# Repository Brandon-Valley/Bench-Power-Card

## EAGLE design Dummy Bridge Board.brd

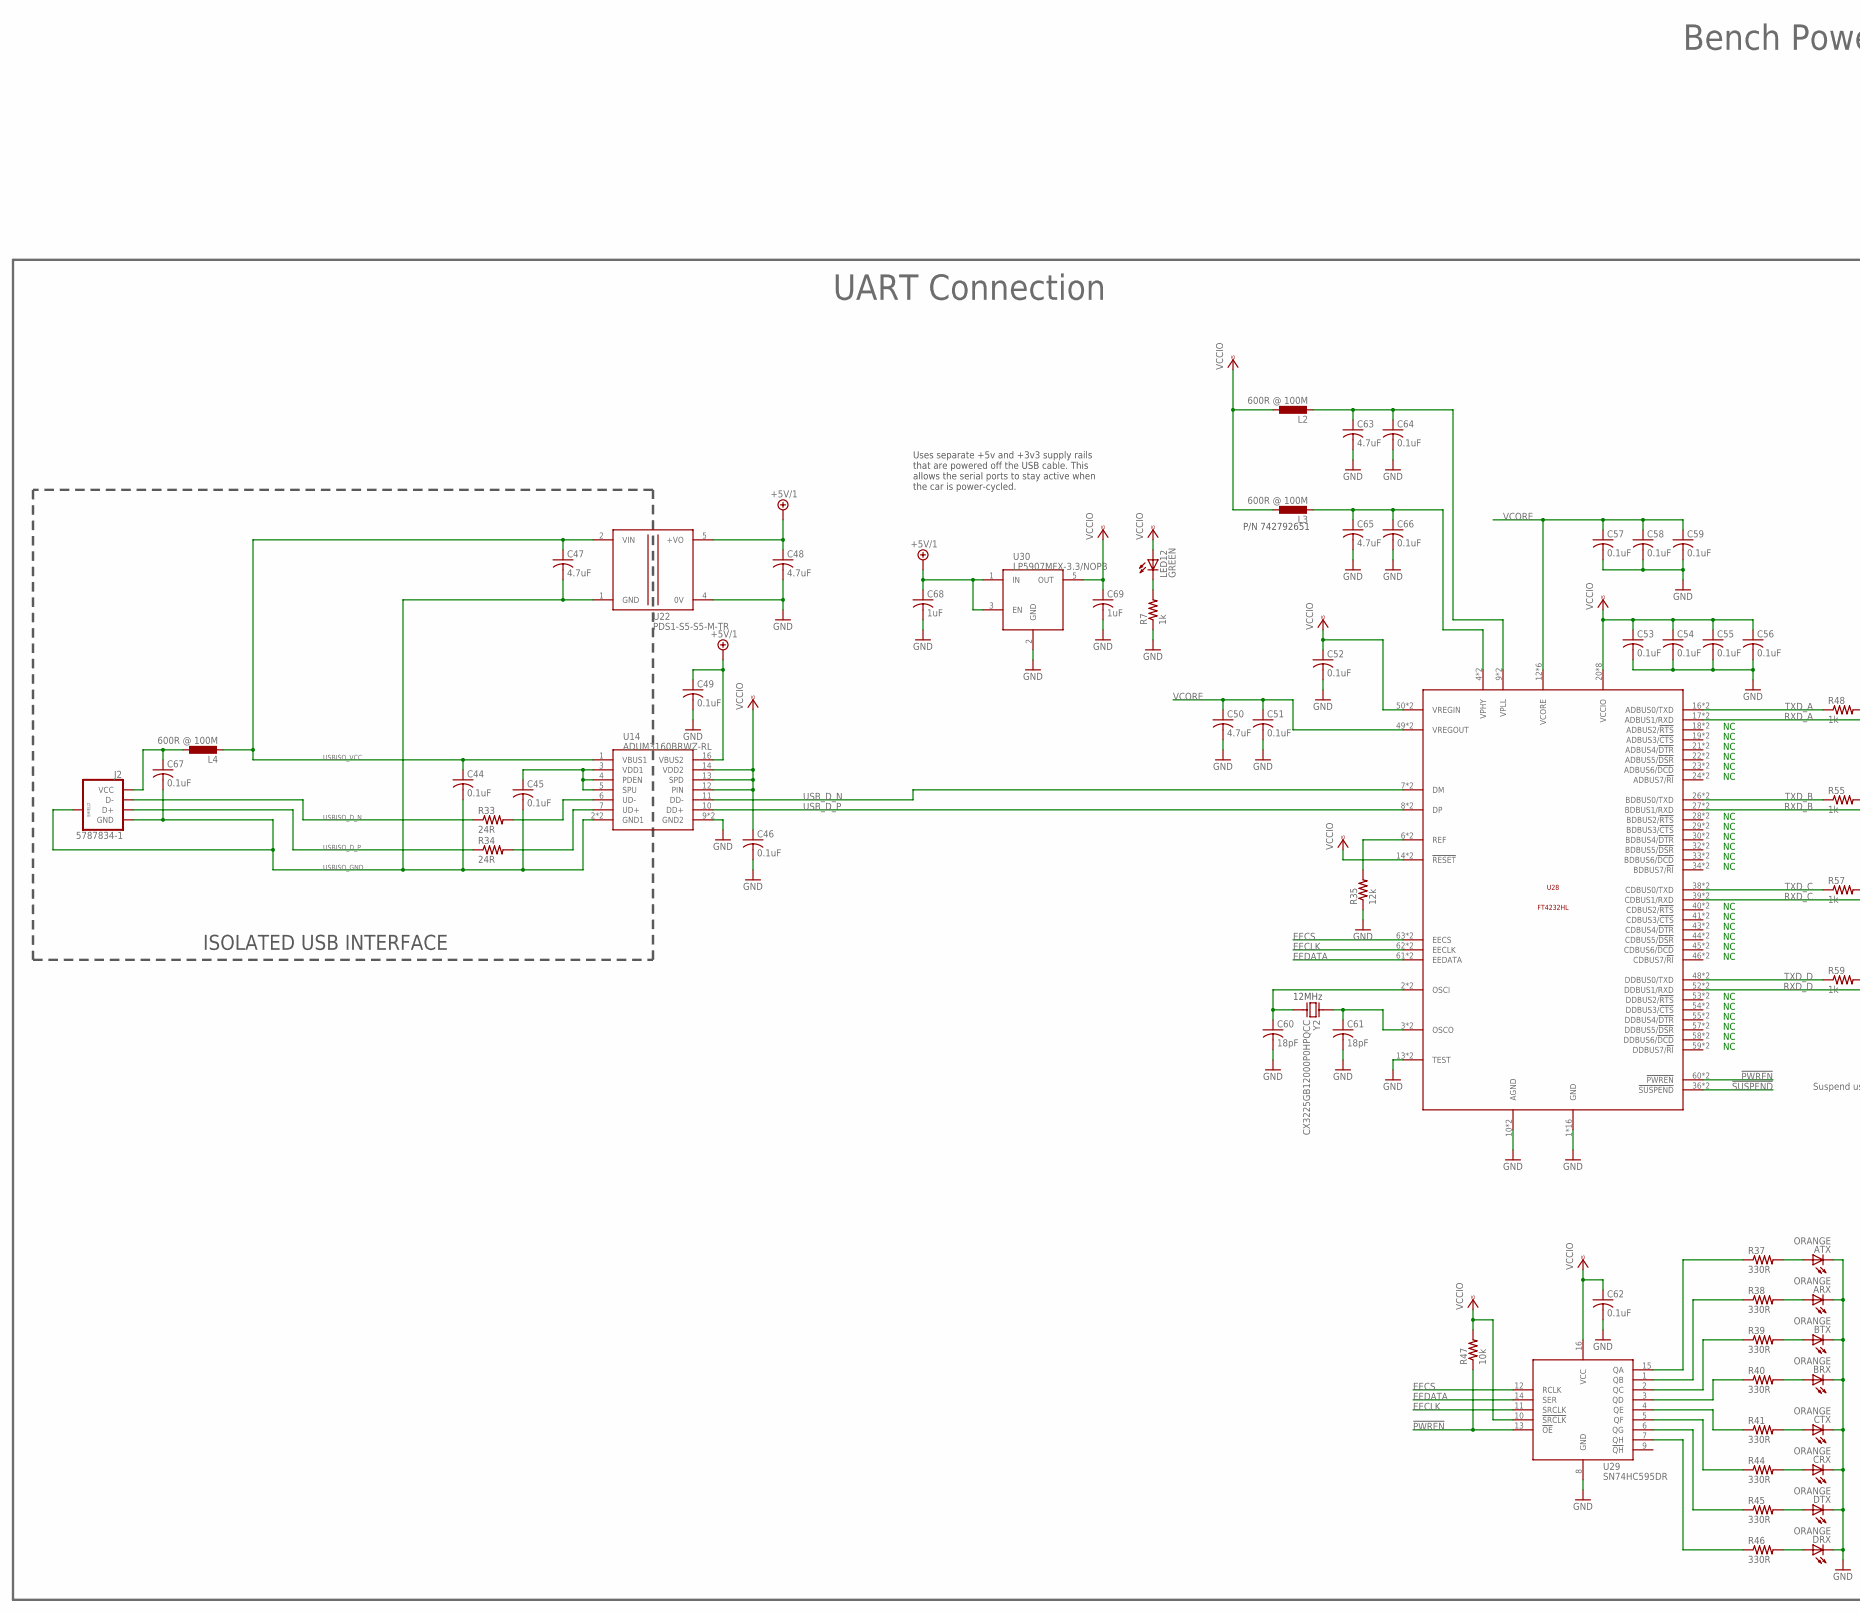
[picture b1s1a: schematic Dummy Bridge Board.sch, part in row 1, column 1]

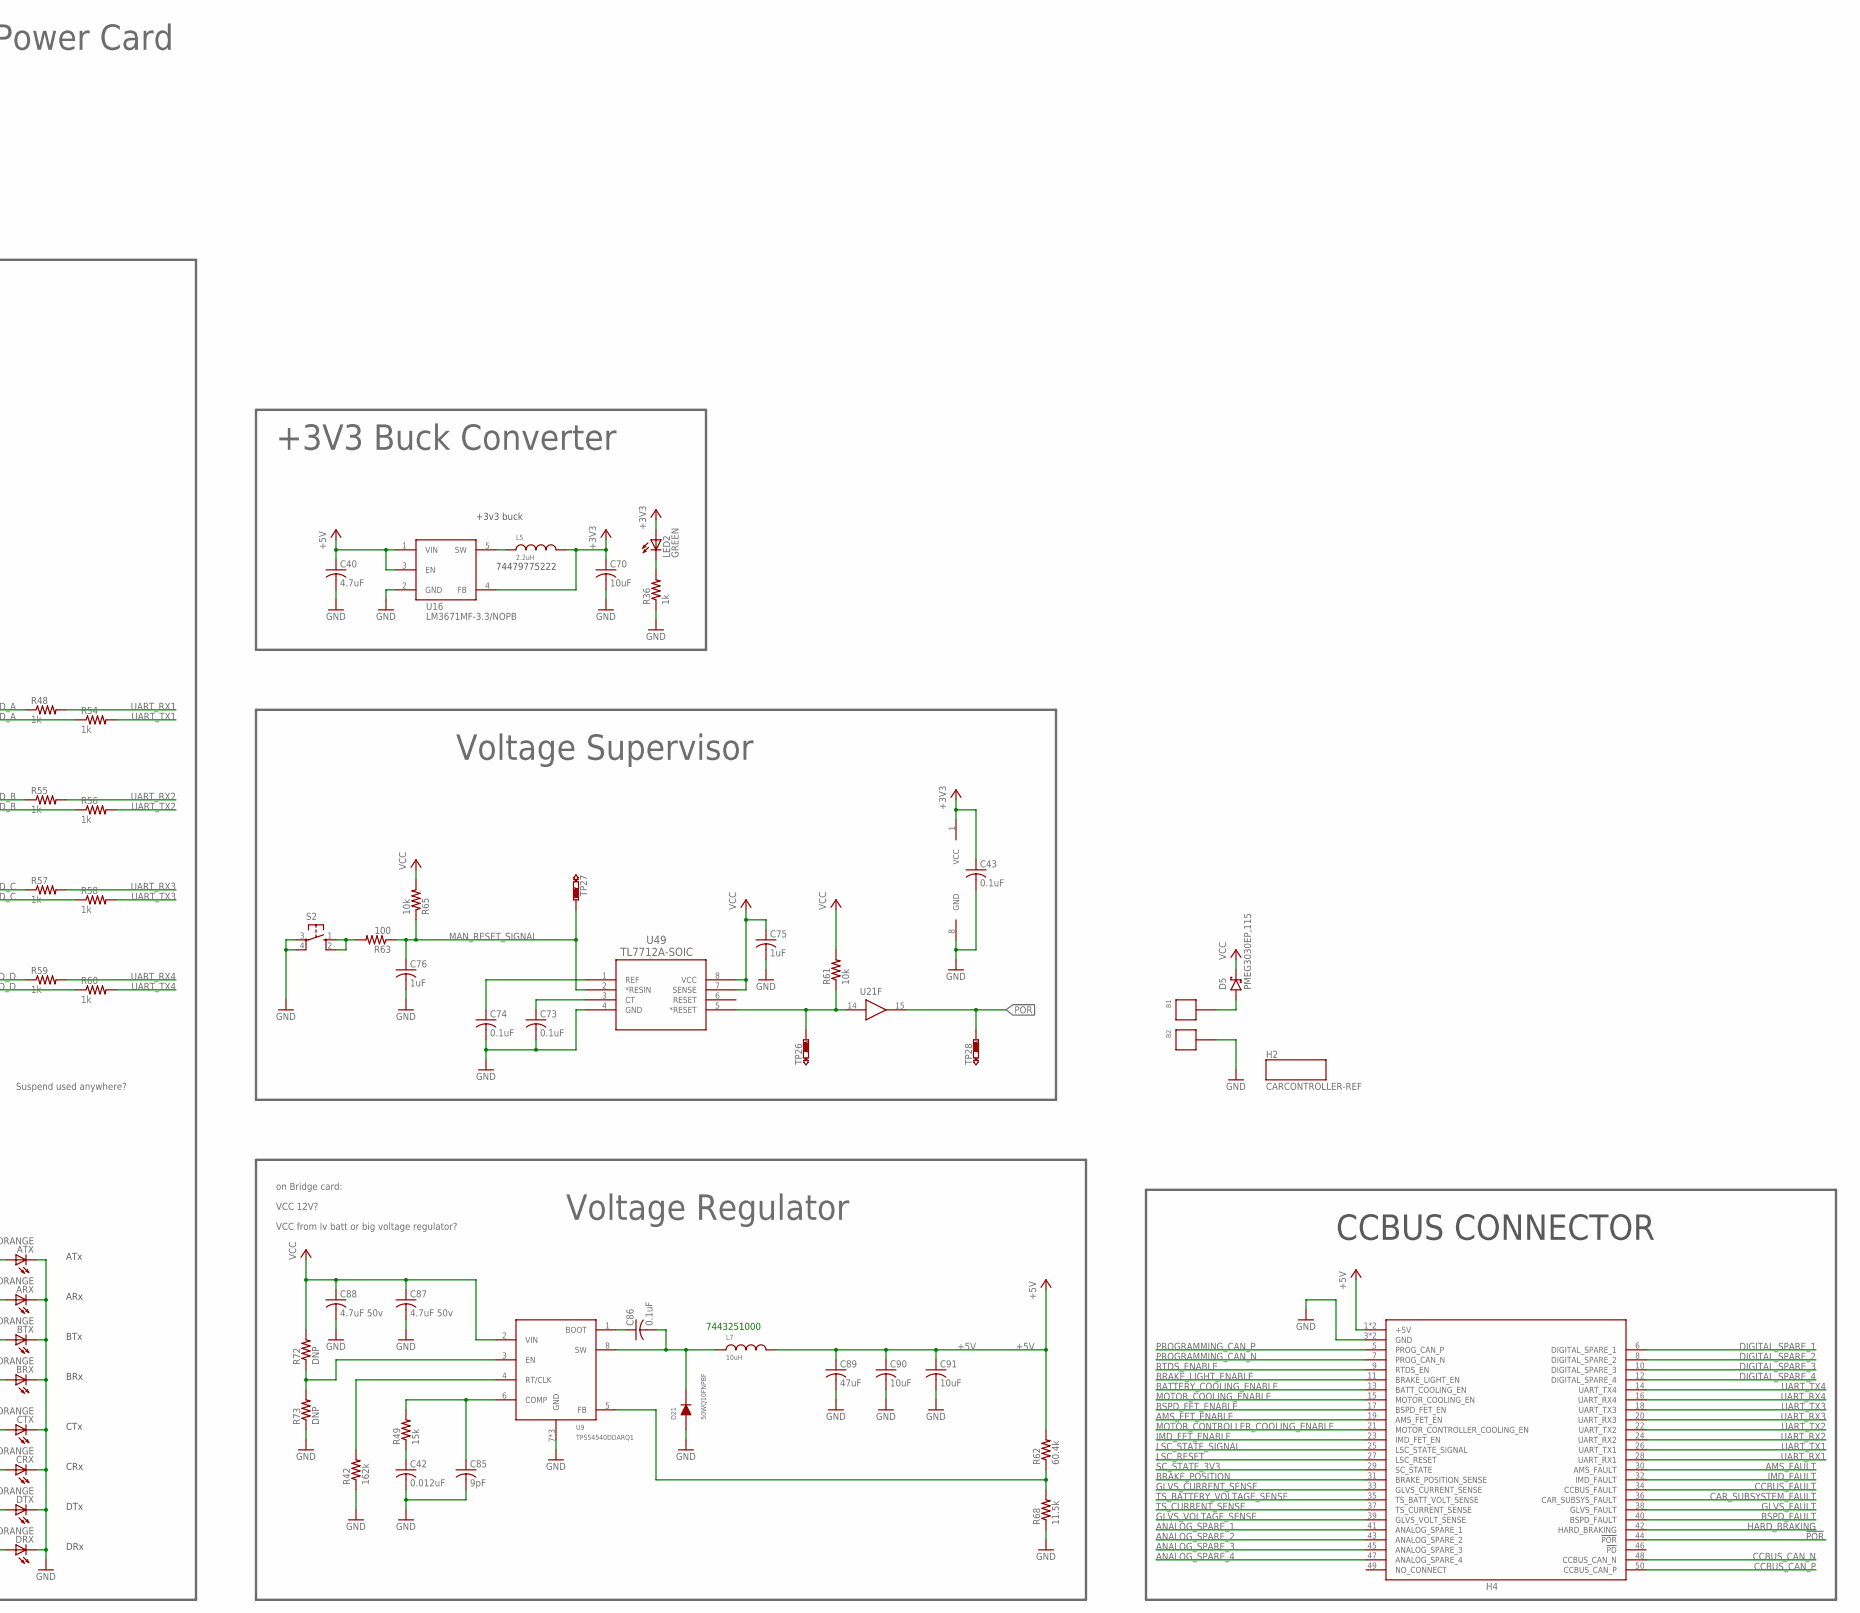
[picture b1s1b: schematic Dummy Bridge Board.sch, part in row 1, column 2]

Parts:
ARX: ORANGE; CHIP-LED0805; PARTNO 598-8130-107F
ATX: ORANGE; CHIP-LED0805; PARTNO 598-8130-107F
B1: BKCT2228-2-ND; BANANA_SOCKET_VERT; PARTNO CT2228-2
B2: BKCT2228-0-ND; BANANA_SOCKET_VERT; PARTNO CT2228-0
BRX: ORANGE; CHIP-LED0805; PARTNO 598-8130-107F
BTX: ORANGE; CHIP-LED0805; PARTNO 598-8130-107F
C40: 4.7uF; C0603K; PARTNO GRM188R61A475KE15D
C42: 0.012uF; C0603K; PARTNO GRM188R71H123KA01D
C43, C44, C45, C46, C49, C51, C52, C53, C54, C55, C56, C57, C58, C59, C62, C64, C66, C67, C86: 0.1uF; C0603K; PARTNO GRM188R71E104KA01D
C47, C48, C50, C63, C65: 4.7uF; C0603K; PARTNO GRM188R61C475KAAJD
C60, C61: 18pF; C0603K; PARTNO GRM1885C1H180JA01D
C68, C69, C75, C76: 1uF; C0603K; PARTNO GRM188R71E104KA01D
C70, C90, C91: 10uF; C0603K; PARTNO EMK107BBJ106MA-T
C73, C74: 0.1uF; C0603K; MPN C2012X7R1H104K085AA
C85: 9pF; C0603K; PARTNO GRM1885C1H9R0DA01D
C87, C88: 4.7uF 50v; C1206; PARTNO GRM31CR71H475KA12L
C89: 47uF; C1206; PARTNO GRM31CR61A476ME15L
CRX: ORANGE; CHIP-LED0805; PARTNO 598-8130-107F
CTX: ORANGE; CHIP-LED0805; PARTNO 598-8130-107F
D5: PMEG3030EP,115; SOD-128; PARTNO PMEG3030EP,115
D21: 50WQ10FNPBF; DPAK; PARTNO VS-50WQ10FNPBF
DRX: ORANGE; CHIP-LED0805; PARTNO 598-8130-107F
DTX: ORANGE; CHIP-LED0805; PARTNO 598-8130-107F
H2: CARCONTROLLER-REF
H4: CCBUS-STACK; SAMTEC-TFM-125-XX-X-D
J2: 5787834-1; TE-5787834-1; PARTNO 5787834-1
L2, L3, L4: 600R @ 100M; 0805; PARTNO BLM21AG601SN1D
L5: 2.2uH; 0805; PARTNO 74479775222
L7: 10uH; WURTH-744325XXXX; PARTNO 7443251000
LED2, LED12: GREEN; CHIP-LED0805; PARTNO 598-8170-107F
R7, R36, R48, R54, R55, R56, R57, R58, R59, R60: 1k; R0603; PARTNO ERJ-3EKF1001V
R33, R34: 24R; R0603; PARTNO ERJ-3EKF24R0V
R35: 12k; R0603; PARTNO ERJ-3EKF1202V
R37, R38, R39, R40, R41, R44, R45, R46: 330R; R0603; PARTNO ERJ-3EKF3300V
R42: 162k; R0603; PARTNO ERJ-3EKF1623V
R47, R61, R65: 10k; R0603; PARTNO ERJ-3EKF1002V
R49: 15k; R0603; PARTNO ERJ-3EKF1502V
R62: 60.4k; R0603; PARTNO ERJ-3EKF6042V
R63: 100; R0603; PARTNO ERJ-3EKF1000V
R68: 11.5k; R0603; PARTNO ERJ-3EKF1152V
R72, R73: DNP; R0603; PARTNO *
S2: TE-FSM4JSMATR; PARTNO FSM4JSMATR
TP26, TP27, TP28: PTR1TP20R; TP20R
U9: TPS54540DDARQ1; TPS54540; PARTNO TPS54540DDAR
U14: ADUM3160BRWZ-RL; ADUM3160; PARTNO ADUM3160BRWZ-RL
U16: LM3671MF-3.3/NOPB; SOT23-5; PARTNO LM3671MF-3.3/NOPB
U21: CD4050BD; SOIC-16; PARTNO CD4050BDR
U22: PDS1-S5-S5-M-TR; PDS1-M; PARTNO PDS1-S5-S5-M-TR
U28: FT4232HL; PQFP-64; PARTNO FT4232HL-REEL
U29: SN74HC595DR; SOIC-16; PARTNO SN74HC595DR
U30: LP5907MFX-3.3/NOPB; SOT23-5; PARTNO LP5907MFX-3.3/NOPB
U49: TL7712A-SOIC; D8; MPN TL7705BID
Y2: CX3225GB12000P0HPQCC; CX3225GB; PARTNO CX3225GB12000P0HPQCC

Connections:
5VREG_EN: R72.1, R73.2, U9.3 (EN)
!POR: H4.44 (!POR!), TP28.TP, U21.15 (OUT)
!PWREN!: R47.1, U28.60 (!PWREN!), U28.MASK-60 (!PWREN!), U29.13 (!OE!)
!SUSPEND!: U28.36 (!SUSPEND!), U28.MASK-36 (!SUSPEND!)
+3V3: C43.1, C70.1, L5.2, LED2.A, U16.4 (FB), U21.1 (VCC)
+5V: C40.1, C89.1, C90.1, C91.1, H4.1 (+5V), H4.2 (+5V), L7.P$2, R62.2, U16.1 (VIN), U16.3 (EN)
+5V/1: C48.1, C49.1, C68.1, U14.16 (VBUS2), U22.5 (+VO), U30.1 (IN), U30.3 (EN)
AMS_FAULT: H4.30 (AMS_FAULT)
AMS_FET_ENABLE: H4.19 (AMS_FET_EN)
ANALOG_SPARE_1: H4.41 (ANALOG_SPARE_1)
ANALOG_SPARE_2: H4.43 (ANALOG_SPARE_2)
ANALOG_SPARE_3: H4.45 (ANALOG_SPARE_3)
ANALOG_SPARE_4: H4.47 (ANALOG_SPARE_4)
BATTERY_COOLING_ENABLE: H4.13 (BATT_COOLING_EN)
BOOT_5V: C86.1, U9.1 (BOOT)
BRAKE_LIGHT_ENABLE: H4.11 (BRAKE_LIGHT_EN)
BRAKE_POSITION: H4.31 (BRAKE_POSITION_SENSE)
BSPD_FAULT: H4.40 (BSPD_FAULT)
BSPD_FET_ENABLE: H4.17 (BSPD_FET_EN)
CAR_SUBSYSTEM_FAULT: H4.36 (CAR_SUBSYS_FAULT)
CCBUS_CAN_N: H4.48 (CCBUS_CAN_N)
CCBUS_CAN_P: H4.50 (CCBUS_CAN_P)
CCBUS_FAULT: H4.34 (CCBUS_FAULT)
COMP_5V: C85.1, R49.2, U9.6 (COMP)
DIGITAL_SPARE_1: H4.6 (DIGITAL_SPARE_1)
DIGITAL_SPARE_2: H4.8 (DIGITAL_SPARE_2)
DIGITAL_SPARE_3: H4.10 (DIGITAL_SPARE_3)
DIGITAL_SPARE_4: H4.12 (DIGITAL_SPARE_4)
EECLK: U28.62 (EECLK), U28.MASK-62 (EECLK), U29.11 (SRCLK)
EECS: U28.63 (EECS), U28.MASK-63 (EECS), U29.12 (RCLK)
EEDATA: U28.61 (EEDATA), U28.MASK-61 (EEDATA), U29.14 (SER)
FB_5V: R62.1, R68.2, U9.5 (FB)
GLVS_CURRENT_SENSE: H4.33 (GLVS_CURRENT_SENSE)
GLVS_FAULT: H4.38 (GLVS_FAULT)
GLVS_VOLTAGE_SENSE: H4.39 (GLVS_VOLT_SENSE)
GND: ARX.C, ATX.C, B2.P$1, BRX.C, BTX.C, C40.2, C42.2, C43.2, C46.2, C48.2, C49.2, C50.2, C51.2, C52.2, C53.2, C54.2, C55.2, C56.2, C57.2, C58.2, C59.2, C60.2, C61.2, C62.2, C63.2, C64.2, C65.2, C66.2, C68.2, C69.2, C70.2, C73.2, C74.2, C75.2, C76.2, C85.2, C87.2, C88.2, C89.2, C90.2, C91.2, CRX.C, CTX.C, D21.1 (ANODE), D21.3 (ANODE), DRX.C, DTX.C, H4.3 (GND), H4.4 (GND), R7.1, R35.1, R36.1, R42.1, R68.1, R73.1, S2.3, S2.4, U9.7 (GND), U9.PAD (GND), U9.PAD1 (GND), U14.9 (GND2), U14.15 (GND2), U16.2 (GND), U21.8 (GND), U22.4 (0V), U28.1 (GND), U28.5 (GND), U28.10 (AGND), U28.11 (GND), U28.13 (TEST), U28.15 (GND), U28.25 (GND), U28.35 (GND), U28.47 (GND), U28.51 (GND), U28.MASK-1 (GND), U28.MASK-5 (GND), U28.MASK-10 (AGND), U28.MASK-11 (GND), U28.MASK-13 (TEST), U28.MASK-15 (GND), U28.MASK-25 (GND), U28.MASK-35 (GND), U28.MASK-47 (GND), U28.MASK-51 (GND), U29.8 (GND), U30.2 (GND), U49.4 (GND)
HARD_BRAKING: H4.42 (HARD_BRAKING)
IMD_FAULT: H4.32 (IMD_FAULT)
IMD_FET_ENABLE: H4.23 (IMD_FET_EN)
LSC_RESET: H4.27 (LSC_RESET)
LSC_STATE_SIGNAL: H4.25 (LSC_STATE_SIGNAL)
MAN_RESET_SIGNAL: C76.1, R63.1, R65.1, TP27.TP, U49.2 (*RESIN)
MOTOR_CONTROLLER_COOLING_ENABLE: H4.21 (MOTOR_CONTROLLER_COOLING_EN)
MOTOR_COOLING_ENABLE: H4.15 (MOTOR_COOLING_EN)
unnamed: B1.P$1, D5.ANODE (A)
unnamed: LED12.C, R7.2
unnamed: C42.1, R49.1
unnamed: R40.1, U29.3 (QD)
unnamed: R41.1, U29.4 (QE)
unnamed: R39.1, U29.2 (QC)
unnamed: R38.1, U29.1 (QB)
unnamed: R37.1, U29.15 (QA)
unnamed: R44.1, U29.5 (QF)
unnamed: LED2.C, R36.2
unnamed: L5.1, U16.5 (SW)
unnamed: R61.1, TP26.TP, U21.14 (IN), U49.5 (*RESET)
unnamed: R45.1, U29.6 (QG)
unnamed: R46.1, U29.7 (QH)
unnamed: ATX.A, R37.2
unnamed: ARX.A, R38.2
unnamed: BTX.A, R39.2
unnamed: BRX.A, R40.2
unnamed: CTX.A, R41.2
unnamed: CRX.A, R44.2
unnamed: DTX.A, R45.2
unnamed: DRX.A, R46.2
unnamed: C67.1, J2.1 (VCC), L4.1
unnamed: C74.1, U49.1 (REF)
unnamed: C73.1, U49.3 (CT)
unnamed: R63.2, S2.1, S2.2
OSCI: C60.1, U28.2 (OSCI), U28.MASK-2 (OSCI), Y2.3
OSCO: C61.1, U28.3 (OSCO), U28.MASK-3 (OSCO), Y2.1
PROGRAMMING_CAN_N: H4.7 (PROG_CAN_N)
PROGRAMMING_CAN_P: H4.5 (PROG_CAN_P)
REF: R35.2, U28.6 (REF), U28.MASK-6 (REF)
RTDS_ENABLE: H4.9 (RTDS_EN)
RT_5V: R42.2, U9.4 (RT/CLK)
RXD_A: R54.1, U28.17 (ADBUS1/RXD), U28.MASK-17 (ADBUS1/RXD)
RXD_B: R56.1, U28.27 (BDBUS1/RXD), U28.MASK-27 (BDBUS1/RXD)
RXD_C: R58.1, U28.39 (CDBUS1/RXD), U28.MASK-39 (CDBUS1/RXD)
RXD_D: R60.1, U28.52 (DDBUS1/RXD), U28.MASK-52 (DDBUS1/RXD)
SC_STATE_3V3: H4.29 (SC_STATE)
SW_5V: C86.2, D21.2 (CATHODE), L7.P$1, U9.8 (SW)
TS_BATTERY_VOLTAGE_SENSE: H4.35 (TS_BATT_VOLT_SENSE)
TS_CURRENT_SENSE: H4.37 (TS_CURRENT_SENSE)
TXD_A: R48.1, U28.16 (ADBUS0/TXD), U28.MASK-16 (ADBUS0/TXD)
TXD_B: R55.1, U28.26 (BDBUS0/TXD), U28.MASK-26 (BDBUS0/TXD)
TXD_C: R57.1, U28.38 (CDBUS0/TXD), U28.MASK-38 (CDBUS0/TXD)
TXD_D: R59.1, U28.48 (DDBUS0/TXD), U28.MASK-48 (DDBUS0/TXD)
UART_RX1: H4.28 (UART_RX1), R48.2
UART_RX2: H4.24 (UART_RX2), R55.2
UART_RX3: H4.20 (UART_RX3), R57.2
UART_RX4: H4.16 (UART_RX4), R59.2
UART_TX1: H4.26 (UART_TX1), R54.2
UART_TX2: H4.22 (UART_TX2), R56.2
UART_TX3: H4.18 (UART_TX3), R58.2
UART_TX4: H4.14 (UART_TX4), R60.2
UD_N: R33.2, U14.6 (UD-)
UD_P: R34.2, U14.7 (UD+)
USBISO_D_N: J2.2 (D-), R33.1
USBISO_D_P: J2.3 (D+), R34.1
USBISO_GND: C44.2, C45.2, C47.2, C67.2, J2.4 (GND), J2.SH1 (SHIELD), J2.SH2 (SHIELD), U14.2 (GND1), U14.8 (GND1), U22.1 (GND)
USBISO_VCC: C44.1, C47.1, L4.2, U14.1 (VBUS1), U22.2 (VIN)
USB_D_N: U14.11 (DD-), U28.7 (DM), U28.MASK-7 (DM)
USB_D_P: U14.10 (DD+), U28.8 (DP), U28.MASK-8 (DP)
VCC: C75.1, C87.1, C88.1, D5.CATHODE (K), R61.2, R65.2, R72.2, U9.2 (VIN), U49.7 (SENSE), U49.8 (VCC)
VCCIO: C46.1, C52.1, C53.1, C54.1, C55.1, C56.1, C62.1, C69.1, L2.1, L3.1, LED12.A, R47.2, U14.12 (PIN), U14.13 (SPD), U14.14 (VDD2), U28.14 (!RESET!), U28.20 (VCCIO), U28.31 (VCCIO), U28.42 (VCCIO), U28.50 (VREGIN), U28.56 (VCCIO), U28.MASK-14 (!RESET!), U28.MASK-20 (VCCIO), U28.MASK-31 (VCCIO), U28.MASK-42 (VCCIO), U28.MASK-50 (VREGIN), U28.MASK-56 (VCCIO), U29.10 (!SRCLK!), U29.16 (VCC), U30.5 (OUT)
VCORE: C50.1, C51.1, C57.1, C58.1, C59.1, U28.12 (VCORE), U28.37 (VCORE), U28.49 (VREGOUT), U28.64 (VCORE), U28.MASK-12 (VCORE), U28.MASK-37 (VCORE), U28.MASK-49 (VREGOUT), U28.MASK-64 (VCORE)
VDD1: C45.1, U14.3 (VDD1), U14.4 (PDEN), U14.5 (SPU)
VPHY: C65.1, C66.1, L3.2, U28.4 (VPHY), U28.MASK-4 (VPHY)
VPLL: C63.1, C64.1, L2.2, U28.9 (VPLL), U28.MASK-9 (VPLL)

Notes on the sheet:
7443251000
Voltage Regulator
VCC 12V?
VCC from lv batt or big voltage regulator?
CCBUS CONNECTOR
ISOLATED USB INTERFACE
P/N 742792651
12MHz
Uses separate +5v and +3v3 supply rails that are powered off the USB cable. This allows the serial ports to stay active when the car is power-cycled.
ATx
ARx
BTx
BRx
CTx
CRx
DTx
DRx
Suspend used anywhere?
UART Connection
on Bridge card:
Bench Power Card
Voltage Supervisor
+3v3 buck
74479775222
+3V3 Buck Converter

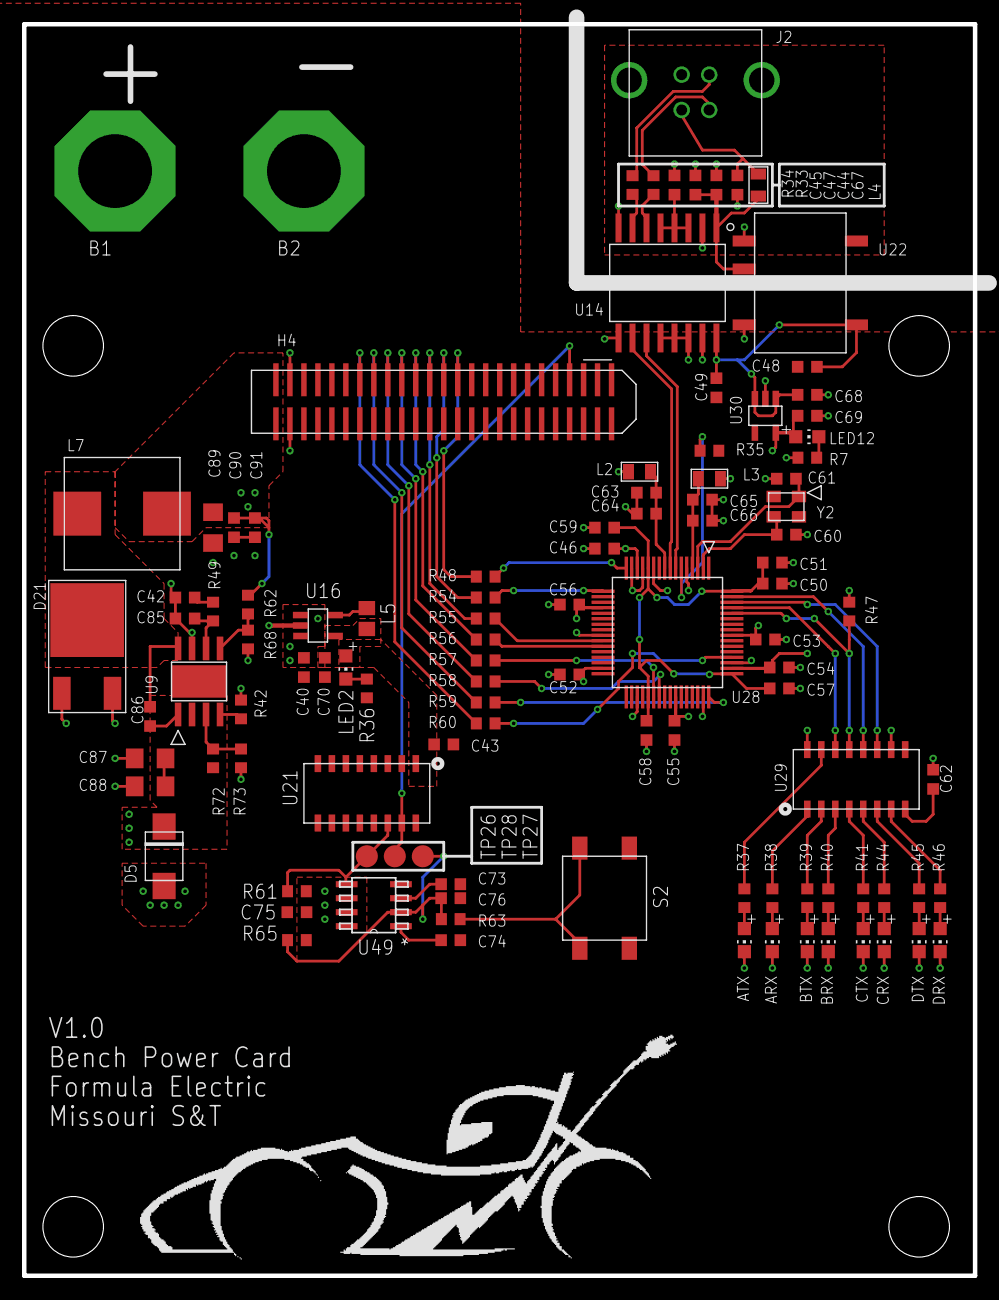
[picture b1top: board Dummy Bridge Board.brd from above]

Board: 2 copper layers, 86.4 x 113.7 mm, 108 parts (0 on the bottom side), 76 nets.

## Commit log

2016-09-01 Dummy Bridge Board: This board will serve as a testing platform for the control system boards that would normaly require the bridge card to run
2016-09-04 DONE- added vert banana sockets
2016-09-06 Added BOM
2016-09-07 Added Voltage supervisor, about to finish BOM
2016-09-07 BOM Exported and minor board change- ready to order
2016-09-07 Added +3V3 Buck and finished BOM- Ready to order
2016-09-07 Fixed BOM and made lines all nice and pretty
2016-09-07 Fixed numerous errors in BOM with wrong part values and packages
